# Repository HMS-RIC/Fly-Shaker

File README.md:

# Fly-Shaker
Deliver vibration stimulus to sleep deprive flies for arousal threshold screening

List of parts, designs and materials to replicate the shaker setup

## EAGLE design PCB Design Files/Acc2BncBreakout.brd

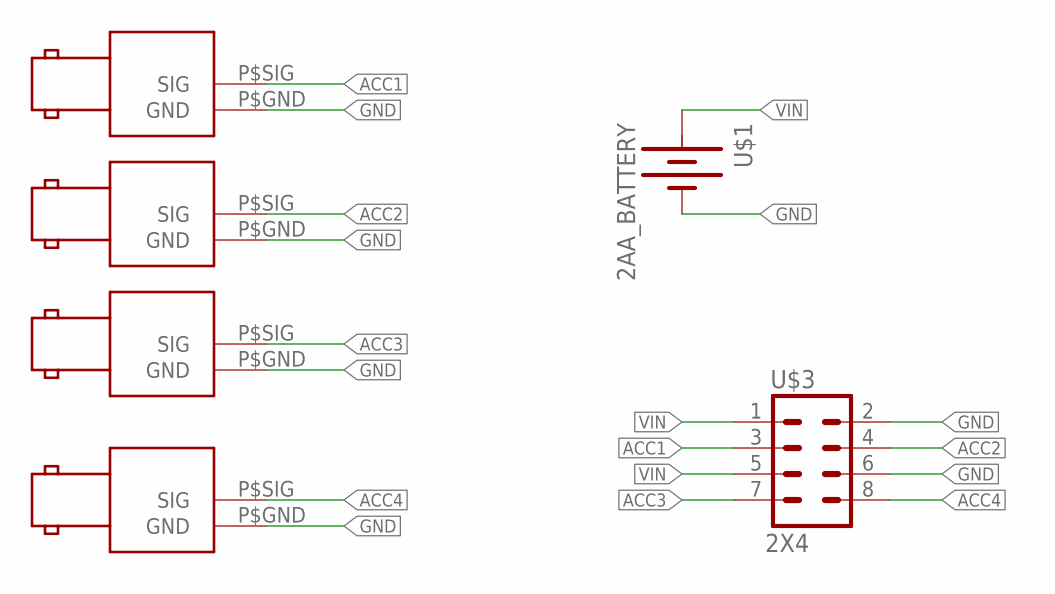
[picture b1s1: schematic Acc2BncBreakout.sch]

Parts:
ACC1, ACC2, ACC3, ACC4: BNC_RIGHT_ANGLE
U$1: 2AA_BATTERY; 2AA_PLASTIC_HOLDER
U$3: 2X4; 2X4_SHROUDED_BERG

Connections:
ACC1: ACC1.P$SIG (SIG), U$3.3
ACC2: ACC2.P$SIG (SIG), U$3.4
ACC3: ACC3.P$SIG (SIG), U$3.7
ACC4: ACC4.P$SIG (SIG), U$3.8
GND: ACC1.P$GND (GND), ACC2.P$GND (GND), ACC3.P$GND (GND), ACC4.P$GND (GND), U$1.PWR@4 (-), U$3.2, U$3.6
VIN: U$1.PWR@3 (+), U$3.1, U$3.5

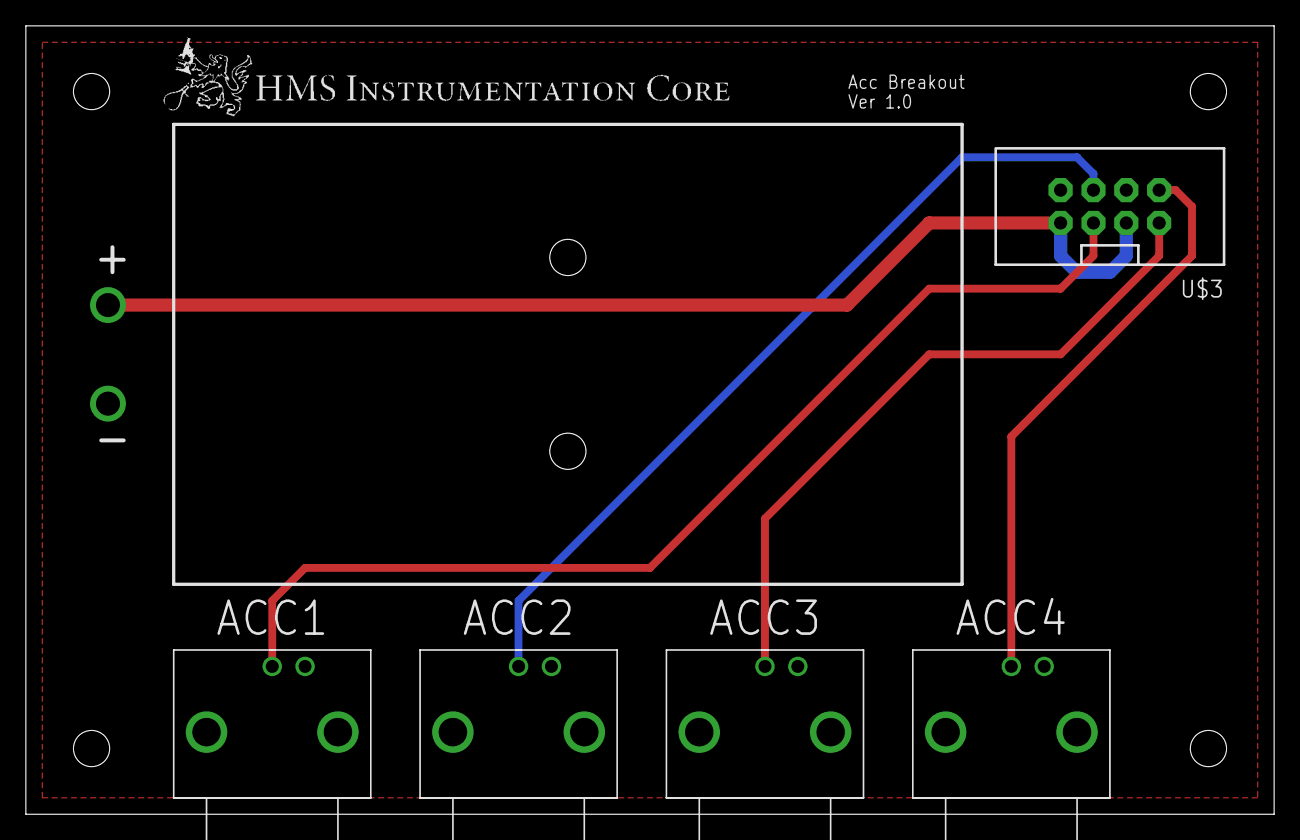
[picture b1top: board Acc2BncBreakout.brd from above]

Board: 2 copper layers, 96.5 x 61.0 mm, 6 parts (0 on the bottom side), 6 nets.

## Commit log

2020-06-19 Create test
2020-06-19 Create test
